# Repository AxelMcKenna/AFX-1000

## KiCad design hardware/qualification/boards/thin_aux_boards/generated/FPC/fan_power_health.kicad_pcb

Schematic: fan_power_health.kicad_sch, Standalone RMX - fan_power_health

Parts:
C1, C2: 10uF 25V C3225X7R1E106K250AC; Capacitor_SMD__C_1210_3225Metric
C3, C14, C22, C23: 10nF 50V C0G C1206C103J5GACTU; Capacitor_SMD__C_1206_3216Metric
C4, C5, C6, C8, C9, C10, C11, C12, C13, C15, C16, C17, C18, C19, C24: 100nF 25V C0G C1206C104J3GACTU; Capacitor_SMD__C_1206_3216Metric
C7: 2.7nF 50V C0G5% C0603C272J5GACTU; Capacitor_SMD__C_0603_1608Metric
C20, C21: 15pF 50V C0G5% C0603C150J5GACTU; Capacitor_SMD__C_0603_1608Metric
C201, C202, C301, C302: 100nF25V C0G5% C1206C104J3GACTU; Capacitor_SMD__C_1206_3216Metric
C203, C303: 1uF63V10% WIMA MKS2C041001F00KSSD; Capacitor_THT__C_Rect_L7.2mm_W5.0mm_P5.00mm
C401, C402, C403, C404: 100nF50V X7R10% C0603C104K5RACTU - EFFECTIVE60nF_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; Capacitor_SMD__C_0603_1608Metric
J2, J3, J4, J201: JST B2B-XH-A / XHP-2 / SXH-001T-P0.6; Connector_JST__JST_XH_B2B-XH-A_1x02_P2.50mm_Vertical
J5: AVRISP2x3 target-powered3.3V sense ONLY; Connector_PinHeader_2.54mm__PinHeader_2x03_P2.54mm_Vertical
J202, J203: JST B3B-XH-A / XHP-3 / SXH-001T-P0.6; Connector_JST__JST_XH_B3B-XH-A_1x03_P2.50mm_Vertical
J401: JST B2B-PH-K-S / PHR-2 / SPH-002T-P0.5S; Connector_JST__JST_PH_B2B-PH-K_1x02_P2.00mm_Vertical
R1, R16, R17, R21, R23: 1k 0.1%25ppm TNPW08051K00BEEA; Resistor_SMD__R_0805_2012Metric
R2, R6, R10, R13, R202, R302: 10k 0.1%25ppm TNPW080510K0BEEA; Resistor_SMD__R_0805_2012Metric
R3, R4, R5, R7, R14, R15: 47k 0.1%25ppm TNPW080547K0BEEA; Resistor_SMD__R_0805_2012Metric
R8: 68k 0.1%25ppm TNPW080568K0BEEA; Resistor_SMD__R_0805_2012Metric
R9: 39k 0.1%25ppm TNPW080539K0BEEA; Resistor_SMD__R_0805_2012Metric
R11: 56.2k 0.1%25ppm TNPW080556K2BEEA; Resistor_SMD__R_0805_2012Metric
R12, R24, R201, R203, R301, R303: 100k 0.1%25ppm TNPW0805100KBEEA; Resistor_SMD__R_0805_2012Metric
R20, R22: 20k 0.1%25ppm TNPW080520K0BEEA; Resistor_SMD__R_0805_2012Metric
R401: 220k 0.1%25ppm TNPW0805220KBEEA - COMPLETE1% RECE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; Resistor_SMD__R_0805_2012Metric
U1: ATtiny84A-SSUR; Package_SO__SOIC-14_3.9x8.7mm_P1.27mm
U2: TPS7A1633DGNR; TI_DGN0008C
U3: SN74LVC2G17DCKR; Package_TO_SOT_SMD__SOT-363_SC-70-6
U4: TPS3431SDRBR; Package_SON__VSON-8-1EP_3x3mm_P0.65mm_EP1.65x2.4mm
U5: SN74AUP1G17DCKR; Package_TO_SOT_SMD__SOT-353_SC-70-5
U6: SN74LVC1T45DBVR; Package_TO_SOT_SMD__SOT-23-6
U7: SN74LVC1G14DCKR; Package_TO_SOT_SMD__SOT-353_SC-70-5
U8: SN74LVC1G74DCUR; TI_DCU0008A
U9: TPS389001DSET; Package_SON__WSON-6_1.5x1.5mm_P0.5mm
U10, U11: SN74LVC1G17DCKR; Package_TO_SOT_SMD__SOT-353_SC-70-5
U12, U13: SN74LVC1G08DCKR; Package_TO_SOT_SMD__SOT-353_SC-70-5
U14: SN74LVC1G06DCKR; Package_TO_SOT_SMD__SOT-353_SC-70-5
U15: TLP175A(TPL,E); RMX_FH02__TLP175A_11-4M1S_Receiving
U16: SN74LVC1G34DCKR; Package_TO_SOT_SMD__SOT-353_SC-70-5
U201, U301: TPS2553DBVR-1; Package_TO_SOT_SMD__SOT-23-6
U401: TPS2553DBVR-1; TI_DBV0006A
X1: ABLS-4.000MHZ-12-D4Y-T; RMX_FH02__ABLS_Manufacturer_Land

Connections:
/E28_POWER_RUN: J4.2 (TO_E28_J5_3), U15.6 (CONTACT_B)
/FAN5V_IN: C1.1, C10.1, C11.1, C12.1, C13.1, C15.1, C201.1, C202.1, C301.1, C302.1, C401.1, C402.1, J201.1 (FAN5V_IN), R1.1, R10.1, R11.1, U2.5 (EN), U2.8 (IN), U6.6 (VCCB), U7.5 (VCC), U8.2 (D), U8.7 (PRE_N), U8.8 (VCC), U9.3 (MR_N), U9.4 (VDD), U10.5 (VCC), U201.1 (IN), U201.3 (EN), U301.1 (IN), U301.3 (EN), U401.1 (IN), U401.3 (EN)
/FAN_L_5V: C203.1, J202.2 (FAN_L_5V), R202.1, R203.1, U201.6 (OUT)
/FAN_L_ILIM: R201.1, U201.5 (ILIM)
/FAN_L_TACH: J202.3 (FAN_L_TACH), R14.1, R202.2, U3.1 (1A)
/FAN_R_5V: C303.1, J203.2 (FAN_R_5V), R302.1, R303.1, U301.6 (OUT)
/FAN_R_ILIM: R301.1, U301.5 (ILIM)
/FAN_R_TACH: J203.3 (FAN_R_TACH), R15.1, R302.2, U3.3 (2A)
/FAULT_CLK: U7.4 (Y), U8.1 (CLK)
/GND: C1.2, C2.2, C3.2, C4.2, C5.2, C6.2, C7.2, C8.2, C9.2, C10.2, C11.2, C12.2, C13.2, C14.2, C15.2, C16.2, C17.2, C18.2, C19.2, C20.2, C21.2, C22.2, C23.2, C24.2, C201.2, C202.2, C203.2, C301.2, C302.2, C303.2, C401.2, C402.2, C403.2, C404.2, J2.2 (GND), J3.2 (GND), J5.6 (GND), J201.2 (FAN_GND), J202.1 (FAN_GND), J203.1 (FAN_GND), J401.2 (GND), R3.2, R4.2, R8.2, R9.2, R12.2, R13.2, R14.2, R15.2, R24.2, R201.2, R203.2, R301.2, R303.2, R401.2, U1.14 (GND), U2.4 (GND), U2.9 (EP), U3.2 (GND), U4.4 (GND), U4.9 (EP), U5.3 (GND), U6.2 (GND), U7.3 (GND), U8.4 (GND), U9.2 (GND), U10.3 (GND), U11.3 (GND), U12.3 (GND), U13.3 (GND), U14.3 (GND), U16.3 (GND), U201.2 (GND), U301.2 (GND), U401.2 (GND)
/HEALTH_AND_WD: U12.4 (Y), U13.1 (A)
/HEARTBEAT: R4.1, U1.11 (PA2), U16.2 (A)
/HEARTBEAT_FAST: U4.6 (WDI), U16.4 (Y)
/HW_NOFAULT: U11.4 (Y), U13.2 (B)
/HW_NOFAULT_5: R9.1, U8.3 (Q_N), U11.2 (A)
/ISP_MISO: J5.1 (ISP_MISO), U1.8 (PA5_MISO)
/ISP_MOSI: J5.4 (ISP_MOSI), U1.7 (PA6_MOSI)
/ISP_SCK: J5.3 (ISP_SCK), U1.9 (PA4_SCK)
/LDO_DELAY: C3.1, U2.7 (DELAY)
/LEAF_PERMISSION: R13.1, U13.4 (Y), U14.2 (A)
/LED_A: R1.2, R2.1, U15.1 (LED_A)
/LED_K: R2.2, U14.4 (Y), U15.3 (LED_K)
/MCU_HEALTH: R3.1, U1.6 (PA7), U12.1 (A)
/MCU_RESET_N: J5.5 (MCU_RESET_N), R6.2, U1.4 (PB3_RESET_N)
/MCU_TACH_L: R16.2, U1.10 (PA3)
/MCU_TACH_R: R17.2, U1.5 (PB2)
/NF_RAW5: C403.1, C404.1, J401.1 (NF_RAW5), U401.6 (OUT)
/NF_RAW5_ILIM: R401.1, U401.5 (ILIM)
/P03_POWER_RUN: J4.1 (FROM_P03_J106_3), U15.4 (CONTACT_A)
/RAW_CLEAR_FAST: U8.6 (CLR_N), U10.4 (Y)
/RAW_CLEAR_N: R10.2, U9.6 (RESET_N), U10.2 (A)
/RAW_POR_CT: C14.1, U9.5 (CT)
/RAW_POR_SENSE: R11.2, R12.1, U9.1 (SENSE)
/TACH_L_BUF: R16.1, U3.6 (1Y)
/TACH_R_BUF: R17.1, U3.4 (2Y)
/TEMP_L_ADC: C22.1, R21.2, U1.13 (PA0_ADC0)
/TEMP_L_NODE: J2.1 (SENSOR), R20.2, R21.1
/TEMP_R_ADC: C23.1, R23.2, U1.12 (PA1_ADC1)
/TEMP_R_NODE: J3.1 (SENSOR), R22.2, R23.1
/V3V3: C2.1, C4.1, C5.1, C6.1, C8.1, C9.1, C16.1, C17.1, C18.1, C19.1, C24.1, J5.2 (V3V3), R5.1, R6.1, R7.1, R20.1, R22.1, R24.1, U1.1 (VCC), U2.1 (OUT), U3.5 (VCC), U4.1 (VDD), U4.5 (SET1), U5.5 (VCC), U6.1 (VCCA), U6.5 (DIR), U11.5 (VCC), U12.5 (VCC), U13.5 (VCC), U14.5 (VCC), U16.5 (VCC)
/WD_CWD: C7.1, U4.2 (CWD)
/WD_EN: R7.2, U4.3 (EN)
/WD_OK: R5.2, U2.3 (PG), U4.7 (WDO_N), U4.8 (ENOUT), U5.2 (A)
/WD_OK_5: R8.1, U6.4 (B), U7.2 (A)
/WD_OK_FAST: U5.4 (Y), U6.3 (A), U12.2 (B)
/XTAL1: C20.1, U1.2 (PB0_XTAL1), X1.1 (XTAL1)
/XTAL2: C21.1, U1.3 (PB1_XTAL2), X1.2 (XTAL2)

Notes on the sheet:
FPC_M2 private successor: third protected NF RAW5 leaf; all84 parent circuits/poses unchanged.
RAW5 operating P03J23/J21 ONLY, neverTESTJ3. No full-source/inrush/physical/PDN acceptance.

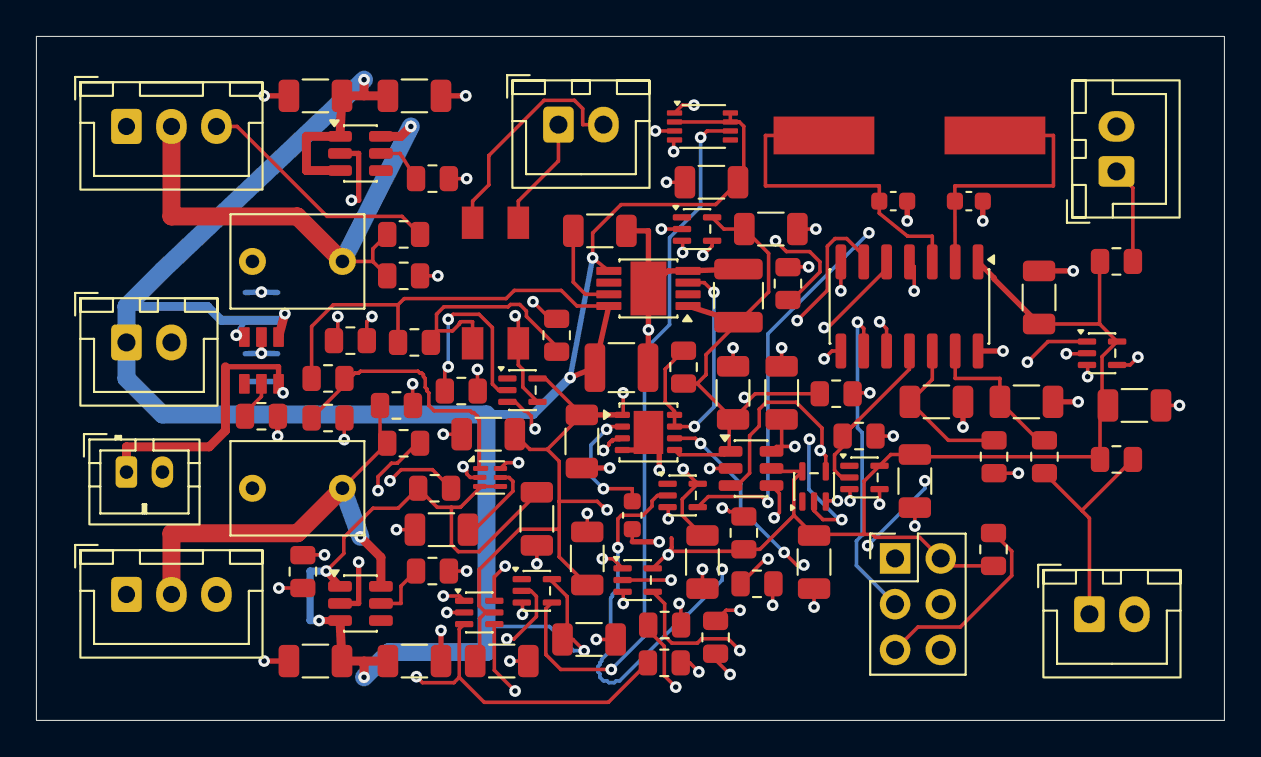
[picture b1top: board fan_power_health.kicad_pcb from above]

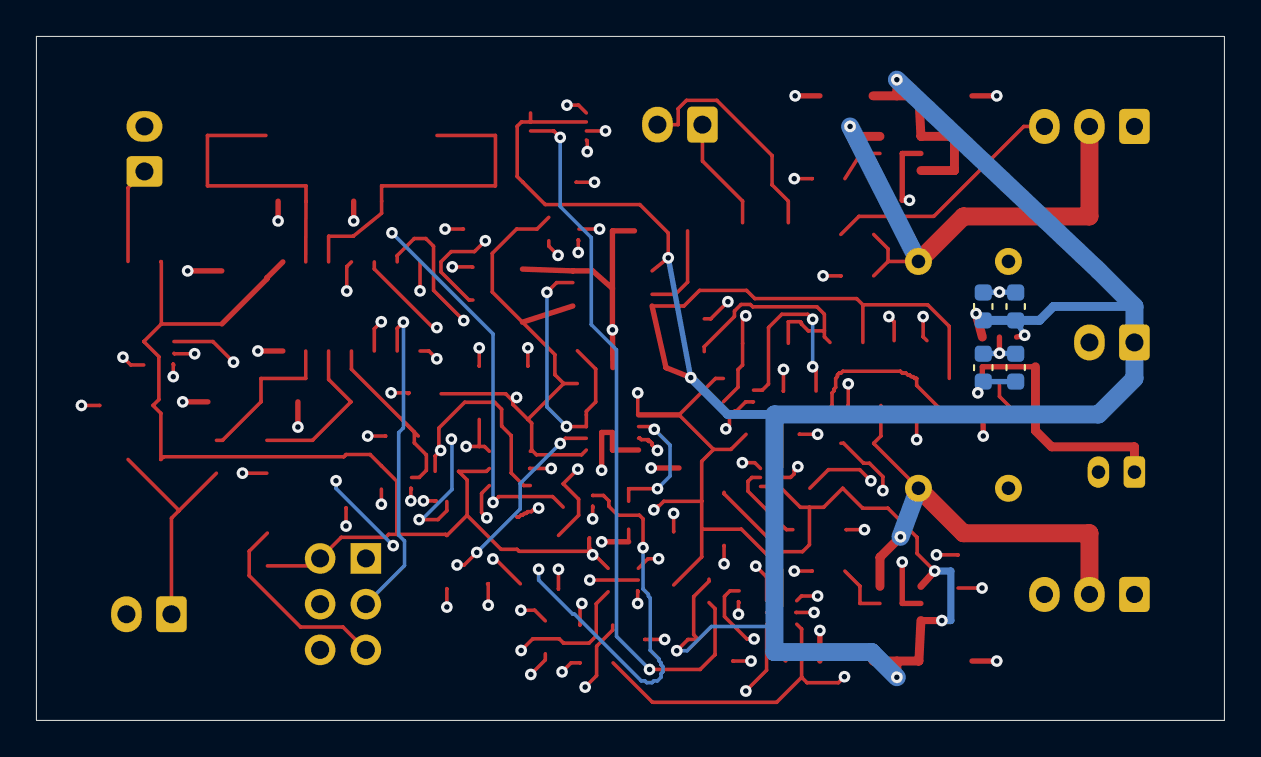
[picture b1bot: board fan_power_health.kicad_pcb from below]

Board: 4 copper layers, 66.0 x 38.0 mm, 91 parts (4 on the bottom side), 47 nets.

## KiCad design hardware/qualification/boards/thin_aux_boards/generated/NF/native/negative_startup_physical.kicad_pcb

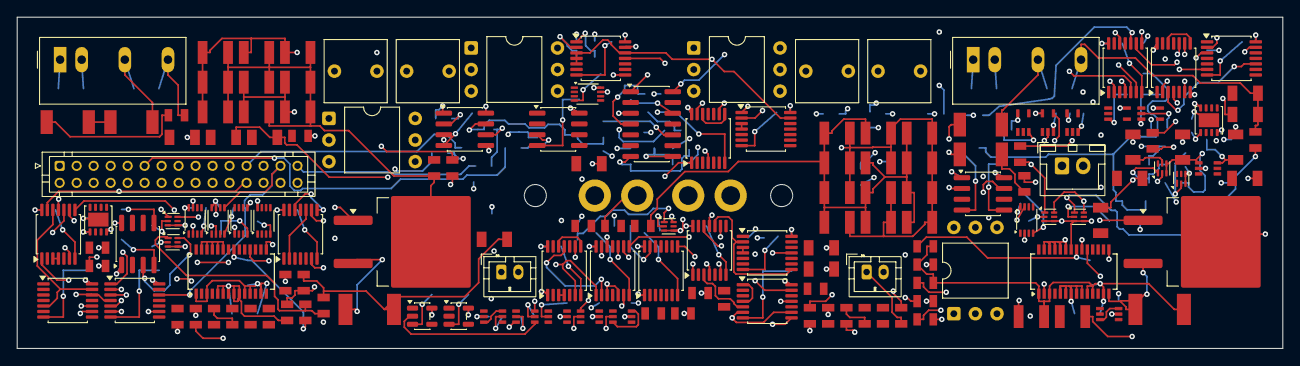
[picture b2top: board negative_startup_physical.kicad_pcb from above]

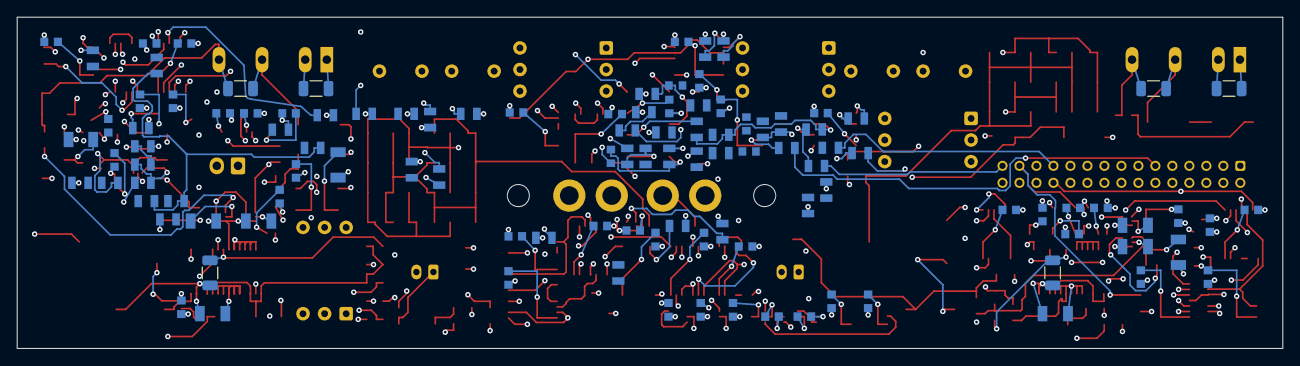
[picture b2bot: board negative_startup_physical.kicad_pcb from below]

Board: 6 copper layers, 149.0 x 39.0 mm, 267 parts (111 on the bottom side), 210 nets.

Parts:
C1: 56nF50V C0G5% C1206C563J5GACTU - COMPLETE10% RECE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; PROPOSED_KEMET1206_LevelB
C2: 33nF50V C0G5% C1206C333J5GACTU - COMPLETE10% RECE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; PROPOSED_KEMET1206_LevelB
C3, C12, C39, C55, C56, C57, C58, C59, C60, C61, C62, C63, C64, C65, C66, C67, C68, C69, C70, C71, C72, C73, C74, C75, C76, C77, C78, C79, C80, C81, C82, C83, C84, C85, C86, C87, C88: 100nF 50V X7R10% C0603C104K5RACTU - bypass effect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; PROPOSED_KEMET0603_LevelB
C4, C31: 10uF 25V X7R MODULE INPUT FILTER/EFFECTIVE/INRUSH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; Capacitor_SMD__C_1206_3216Metric
C5, C32: 1uF 50V X7R MODULE OUTPUT FILTER/EFFECTIVE HOLD; Capacitor_SMD__C_1206_3216Metric
C6, C33: 1uF 25V X7R LTC4261 local VIN effective HOLD; Capacitor_SMD__C_1206_3216Metric
C7, C9, C11, C13, C34, C36, C38, C40: 100nF 25V C0G C1206C104J3GACTU; PROPOSED_KEMET1206_LevelB
C8, C10, C35, C37: 10nF 50V C0G COMPLETE10% TIMING RECEIVING; PROPOSED_KEMET1206_LevelB
C14, C15, C16, C17, C18, C19, C20, C21, C22, C23, C24, C25, C41, C42, C43, C44, C45, C46, C47, C48, C49: 100nF 50V C0G C1210C104J5GACTU - COMPLETE10% RAMP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; PROPOSED_KEMET1210_LevelB
C26, C27, C50, C51: 2.2uF 63V PET5% MKS2C042201K00JSSD - COMPLETE10% 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; Capacitor_THT__C_Rect_L7.2mm_W7.2mm_P5.00mm_FKS2_FKP2_MKS2_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
C28, C30, C52, C54: 47nF 50V C0G C1206C473J5GACTU; PROPOSED_KEMET1206_LevelB
C29, C53: 100nF 50V C0G C1210C104J5GACTU; PROPOSED_KEMET1210_LevelB
C89, C90, C91, C93, C94, C96: 100nF50V X7R10% C0603C104K5RACTU - EFFECTIVE/PDN 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; PROPOSED_KEMET0603_LevelB
C92, C95: 47nF50V C0G5% C1206C473J5GACTU - COMPLETE6% RECEI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; PROPOSED_KEMET1206_LevelB
C97, C98: 100nF25V C0G5% C1206C104J3GACTU - COMPLETE6% CT /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; PROPOSED_KEMET1206_LevelB
C99: 100nF25V C0G5% C1206C104J3GACTU - COMPLETE6% UVRE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; PROPOSED_KEMET1206_LevelB
C100: 100nF50V X7R10% C0603C104K5RACTU - LOCAL_BYPASS_E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; PROPOSED_KEMET0603_LevelB
H101, H102: STRAIN_POST_2p6_NPTH_RECEIVING
J1: NEW NF03C CONTROL/KELVIN INTERFACE - physical con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; NC265_JST_PHD_B30B-PHDSS_2x15_P2.00mm_Vertical
J2: N19 NEW FORCE IN/OUT - connector and harness unse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; NC265_NC265_Force2_18AWG_P5_Drill2p2_Land3p8
J3: N19 E28 BANK GATE/COMMON CLAMP - physical interfa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; NC265_JST_PH_B2B-PH-K_1x02_P2.00mm_Vertical
J4: N12 NEW FORCE IN/OUT - connector and harness unse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; NC265_NC265_Force2_18AWG_P5_Drill2p2_Land3p8
J5: N12 E28 BANK GATE/COMMON CLAMP - physical interfa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; NC265_JST_PH_B2B-PH-K_1x02_P2.00mm_Vertical
J6: NEW MODULE INPUT ONLY - keyed JST XH2 receiving c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; NC265_JST_XH_B2B-XH-A_1x02_P2.50mm_Vertical
Q1, Q2: CSD19536KTT; Package_TO_SOT_SMD__TO-263-2
R1, R2, R8, R9: 10k; PROPOSED_TNPW0805_IPC28950
R3, R10: 205000ohm 0.1% TNPW0805205KBEEA - COMPLETE3% RECE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; PROPOSED_TNPW0805_IPC28950
R4, R11: 499ohm 0.1% TNPW0805499RBEEA - COMPLETE3% RECEIVI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; PROPOSED_TNPW0805_IPC28950
R5, R12, R95, R98, R99: 10000ohm 0.1% TNPW080510K0BEEA - COMPLETE3% RECEI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; PROPOSED_TNPW0805_IPC28950
R6, R7, R13, R14: 220ohm COMPLETE +/-3% RECEIVING; PROPOSED_TNPW0805_IPC28950
R15, R16, R17, R18, R19, R20, R21, R22: 47k 3% TOTAL RECEIVING; PROPOSED_TNPW0805_IPC28950
R23: 160000ohm COMPLETE0.1% RECEIVING; PROPOSED_TNPU0805_IPC28950
R24, R41, R63, R65, R80, R82: 10k COMPLETE0.1% RECEIVING; PROPOSED_TNPU0805_IPC28950
R25, R49: 8660ohm COMPLETE0.1% RECEIVING; PROPOSED_TNPU0805_IPC28950
R26, R50: 35.7ohm COMPLETE0.1% RECEIVING; PROPOSED_TNPU0603_IPC28950
R27, R31, R35, R44, R47, R51: 100k COMPLETE0.1% RECEIVING; PROPOSED_TNPU0805_IPC28950
R28, R32, R36, R37, R38, R39, R45, R48, R52, R53, R54, R55, R59, R76: 10k COMPLETE3% RECEIVING; PROPOSED_TNPW0805_IPC28950
R29, R46: 2000ohm COMPLETE0.1% RECEIVING; PROPOSED_TNPU0805_IPC28950
R30: 40.2ohm COMPLETE0.1% RECEIVING; PROPOSED_TNPU0603_IPC28950
R33: 6040ohm COMPLETE0.1% RECEIVING; PROPOSED_TNPU0805_IPC28950
R34: 75ohm COMPLETE0.1% RECEIVING; PROPOSED_TNPU0603_IPC28950
R40: 102000ohm COMPLETE0.1% RECEIVING; PROPOSED_TNPU0805_IPC28950
R42: 10700ohm COMPLETE0.1% RECEIVING; PROPOSED_TNPU0805_IPC28950
R43: 169ohm COMPLETE0.1% RECEIVING; PROPOSED_TNPU0805_IPC28950
R56, R57, R73, R74: 402ohm 1% CRCW2010402RFKEF - COMPLETE3% RECEIVING; PROPOSED_CRCW2010_reflow20035
R58, R60, R61, R66, R67, R68, R75, R77, R78, R83, R84, R85: 47k COMPLETE3% RECEIVING; PROPOSED_TNPW0805_IPC28950
R62, R79: 30.4k COMPLETE0.1% RECEIVING; PROPOSED_TNPU0805_IPC28950
R64, R81: 78.7k COMPLETE0.1% RECEIVING; PROPOSED_TNPU0805_IPC28950
R69: 0.33ohm COMPLETE5% SHUNT RECEIVING; PROPOSED_WSL2512_7m_to500m
R70, R87: 10ohm COMPLETE3% RECEIVING; PROPOSED_TNPW0805_IPC28950
R71, R88: 1M; PROPOSED_TNPW0805_IPC28950
R72: 27ohm COMPLETE3% RECEIVING; PROPOSED_TNPW0805_IPC28950
R86: 0.12ohm COMPLETE5% SHUNT RECEIVING; PROPOSED_WSL2512_7m_to500m
R89: 39ohm COMPLETE3% RECEIVING; PROPOSED_TNPW0805_IPC28950
R90, R91: 10k0.1% TNPW080510K0BEEA - COMPLETE3% RECEIVING; PROPOSED_TNPW0805_IPC28950
R92: 11300ohm 0.02% 2ppm TNPU080511K3HWEN00 - COMPLETE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; PROPOSED_TNPW0805_IPC28950
R93: 49.9ohm 0.1% TNPW080549R9BEEA - COMPLETE0.7% TRIM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; PROPOSED_TNPW0805_IPC28950
R94: 10000ohm 0.02% 2ppm TNPU080510K0HWEN00 - COMPLETE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; PROPOSED_TNPW0805_IPC28950
R96: 47000ohm 0.1% TNPW080547K0BEEA - COMPLETE3% RECEI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; PROPOSED_TNPW0805_IPC28950
R97: 680ohm 0.1% TNPW1206680RBEEA - COMPLETE3% RECEIVI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; PROPOSED_TNPW1206_IPC28950
U1, U2, U7, U8: SN74AUP1G74DCUR; NF05R_Manufacturer__TI_DCU0008A
U3, U9: TPS3431SDRBR; Package_SON__VSON-8-1EP_3x3mm_P0.65mm_EP1.65x2.4mm
U4, U10: SN74LVC1G06DBVR; Package_TO_SOT_SMD__SOT-23-5
U5, U6, U11, U12: TLP4590AF(F; Package_DIP__DIP-6_W10.16mm
U13: OPA2333AID; Package_SO__SOIC-8_3.9x4.9mm_P1.27mm
U14: TLV1822DR; Package_SO__SOIC-8_3.9x4.9mm_P1.27mm
U15: TLV1824DR; Package_SO__SOIC-14_3.9x8.7mm_P1.27mm
U16, U27: SN74LVC2T45DCUR; NF05R_Manufacturer__TI_DCU0008A
U17, U22: TMR 1-1215; Converter_DCDC__Converter_DCDC_TRACO_TMR-1-xxxx_Single_THT
U18, U23: LTC4261IGN#PBF; Package_SO__SSOP-28_3.9x9.9mm_P0.635mm
U19, U24: ISO7721FDR; Package_SO__SOIC-8_3.9x4.9mm_P1.27mm
U20, U21, U25, U26, U52, U54, U56: TPS389001DSET; Package_SON__WSON-6_1.5x1.5mm_P0.5mm
U28, U30, U53, U55: SN74LVC1G17DCKR; NF05R_Manufacturer__TI_DCK0005A
U29, U31, U32, U33, U34, U49: SN74AUP2G14DCKR; NF05R_Manufacturer__TI_DCK0006A
U35, U36, U37, U38, U39, U40, U41, U42, U43, U44, U51: SN74HCS08PWR; Package_SO__TSSOP-14_4.4x5mm_P0.65mm
U45, U46: SN74HCS32PWR; Package_SO__TSSOP-14_4.4x5mm_P0.65mm
U47, U48: SN74HCS14PWR; Package_SO__TSSOP-14_4.4x5mm_P0.65mm
U50: SN74HCS02PWR; Package_SO__TSSOP-14_4.4x5mm_P0.65mm
U57: TPS22919DCKR; NF05R_Manufacturer__TI_DCK0006A
U58: SN74LVC1G14DCKR; NF05R_Manufacturer__TI_DCK0005A

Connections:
/ABS_AUX_CT: C99.1, U56.5
/ABS_AUX_FAULT: J1.7, R17.1, U48.13, U58.4
/ABS_AUX_READY: U48.12, U51.13
/ABS_AUX_SENSE: R93.2, R94.1, U56.1
/ABS_AUX_TOP_TRIM: R92.2, R93.1
/AGND: C1.2, C2.2, C3.2, C12.2, C39.2, C55.2, C56.2, C57.2, C58.2, C59.2, C60.2, C61.2, C62.2, C63.2, C64.2, C65.2, C66.2, C67.2, C68.2, C69.2, C70.2, C71.2, C72.2, C73.2, C74.2, C75.2, C76.2, C77.2, C78.2, C79.2, C80.2, C81.2, C82.2, C83.2, C84.2, C85.2, C86.2, C87.2, C88.2, C89.2, C90.2, C91.2, C92.2, C93.2, C94.2, C95.2, C96.2, C97.2, C98.2, C99.2, C100.2, J1.2, R3.2, R10.2, R15.2, R16.2, R17.2, R18.2, R19.2, R20.2, R21.2, R22.2, R27.2, R31.2, R35.2, R44.2, R47.2, R51.2, R59.2, R61.2, R67.2, R68.2, R76.2, R78.2, R84.2, R85.2, R94.2, R96.2, R97.2, U1.4, U2.4, U3.4, U3.9, U4.3, U7.4, U8.4, U9.4, U9.9, U10.3, U13.3, U13.4, U13.5, U14.4, U15.12, U16.4, U19.5, U24.5, U27.4, U28.3, U29.2, U30.3, U31.2, U32.2, U33.2, U34.2, U35.7, U36.7, U37.7, U38.7, U39.7, U40.7, U41.7, U42.7, U43.7, U44.7, U45.7, U46.7, U46.12, U46.13, U47.7, U48.7, U49.2, U50.7, U51.7, U52.2, U53.3, U54.2, U55.3, U56.2, U57.2, U58.3
/AUX2V6: C3.1, C12.1, C56.1, C57.1, C58.1, C59.1, C60.1, C61.1, C62.1, C63.1, C64.1, C65.1, C66.1, C67.1, C68.1, C69.1, C70.1, C71.1, C72.1, C73.1, C74.1, C75.1, C76.1, C77.1, C78.1, C79.1, C80.1, C81.1, C82.1, C83.1, C84.1, C85.1, C86.1, C87.1, C88.1, C89.1, C90.1, C91.1, C93.1, C94.1, C96.1, C100.1, J1.1, R1.1, R2.1, R8.1, R9.1, R37.1, R38.1, R39.1, R53.1, R54.1, R55.1, R90.1, R91.1, R92.1, U1.7, U1.8, U2.2, U2.7, U2.8, U3.1, U4.5, U7.7, U7.8, U8.2, U8.7, U8.8, U9.1, U10.5, U13.8, U14.8, U15.3, U16.1, U16.5, U27.8, U28.5, U29.5, U30.5, U31.5, U32.5, U33.5, U34.5, U35.14, U36.14, U37.14, U38.14, U39.14, U40.14, U41.14, U42.14, U43.14, U44.14, U45.14, U46.14, U47.14, U48.14, U49.5, U50.14, U51.14, U52.3, U52.4, U53.5, U54.3, U54.4, U55.5, U58.5
/AUX_VALID: J1.5, R16.1, U35.1
/CLAMP_LED_SUPPLY: C98.1, R4.1, R11.1, R97.1, U57.6
/CLAMP_SUPPLY_ENABLE: R95.2, R96.1, U56.6, U57.3, U58.2
/DIG5_FORCE: C39.1, C55.1, C97.1, J1.3, R95.1, U16.8, U19.8, U24.8, U27.1, U27.5, U56.3, U56.4, U57.1
/E28_COMBINED_FAULT_REQUEST: J1.14, U34.4
/E28_COMBINED_FAULT_REQUEST_BUFFER_MID: U34.3, U34.6
/E28_COMBINED_FAULT_REQUEST_HCS: U34.1, U46.6
/E28_NATIVE_FAULT_REQUEST: J1.13, U46.4
/E28_NOT_FAULT: J1.15, R22.1, U44.4
/GLOBAL_MASTER: J1.6, R15.1, U35.2
/GLOBAL_VALID: U35.3, U35.4, U35.5, U35.12, U37.4, U38.5, U38.13, U40.12, U41.13, U48.11, U51.1, U51.4
/GUARDED_12V_FORCE: C4.1, C31.1, J6.1, U17.2, U22.2
/MODULE_INPUT_GND: C4.2, C31.2, J6.2, U17.1, U22.1
/N12_ARM_CONDITIONED: J1.24, R20.1, U30.4, U39.1, U40.13, U41.12, U54.1
/N12_ARM_Q: U30.2, U50.10, U50.12
/N12_ARM_QBAR: U50.9, U50.13
/N12_ARM_SET: U50.11, U51.8
/N12_BANK_CLAMP_GATE: R14.2, U12.4
/N12_BANK_COMMON: J5.2, U12.6
/N12_BANK_GATE: J5.1, R14.1
/N12_BIAS_CT: C37.1, U25.5
/N12_BIAS_HOST5: R84.1, U24.6, U27.3
/N12_BIAS_RESET_N: R83.2, U24.3, U25.6, U26.6
/N12_BIAS_SENSE: R79.2, R80.1, U25.1
/N12_BIAS_VALID: J1.17, R85.1, U27.6, U43.13
/N12_CG_SERIES: C52.1, R87.2
/N12_CLAMPS_RELEASE: J1.28, R10.1, U10.2, U33.4
/N12_CLAMPS_RELEASE_BUFFER_MID: U33.3, U33.6
/N12_CLAMPS_RELEASE_HCS: U33.1, U42.3
/N12_CLAMP_LED_A: R11.2, R12.1, U11.1
/N12_CLAMP_LED_K: R99.2, U10.4, U12.2
/N12_CLAMP_LED_MID: R12.2, R99.1, U11.2, U12.1
/N12_COMPLETE: J1.27, U8.5, U39.12, U44.12
/N12_COMPLETE_CLK: U8.1, U41.8
/N12_COMPLETE_CLR_N: U8.6, U41.11
/N12_CONTROLLER_ON: R77.1, U23.2, U24.2
/N12_CR_TOP: C41.1, C42.1, C43.1, C44.1, C45.1, C46.1, C47.1, C48.1, C49.1, R89.2
/N12_CWD: C2.1, U9.2
/N12_DRAIN_SENSE: R88.2, U23.16
/N12_E28_SRC: C41.2, C42.2, C43.2, C44.2, C45.2, C46.2, C47.2, C48.2, C49.2, J4.2, Q2.2, R88.1
/N12_F0: U45.8, U45.12
/N12_FAULT_REQUEST: J1.26, U45.11, U46.2
/N12_FEED_MID: R73.2, R74.1
/N12_F_OUTPUT: U39.11, U45.13
/N12_F_SOURCE: U39.3, U45.9
/N12_F_TIMEOUT: U39.8, U45.10
/N12_F_WD_ARM: U39.6, U39.9
/N12_INTVCC: C34.1, C36.1, C38.1, C40.1, R79.1, R83.1, U23.5, U23.6, U23.7, U23.8, U23.9, U23.22, U24.1, U25.3, U25.4, U26.3, U26.4
/N12_ISO24: C32.1, R73.1, U22.4
/N12_NOT_COMPLETE: U8.3, U9.5
/N12_NOT_PERMIT: U7.3, U9.6
/N12_NOT_READY: U39.13, U47.10
/N12_NOT_SAFE: U39.2, U47.8
/N12_NOT_WDO: U39.10, U47.12
/N12_OUTPUT_OV_GOOD: R55.2, U15.13, U43.10, U44.2
/N12_OUTPUT_QUALIFIED: U44.11, U48.5
/N12_OUTPUT_UV_GOOD: R54.2, U15.14, U44.1
/N12_OUT_INV: R41.1, R45.1, R48.1, U13.7
/N12_OUT_OV_REF: R46.2, R47.1, U15.11
/N12_OUT_OV_SENSE: R48.2, U15.10
/N12_OUT_SUM: R40.2, R41.2, U13.6
/N12_OUT_UV_REF: R43.2, R44.1, U15.8
/N12_OUT_UV_RMID: R42.2, R43.1
/N12_OUT_UV_SENSE: R45.2, U15.9
/N12_OV_OK: J1.10, U43.5
/N12_OV_SENSE: J1.12, R52.1
/N12_P03_SRC: C32.2, C33.2, C34.2, C35.2, C36.2, C37.2, C38.2, C40.2, C50.2, C51.2, C52.2, C53.2, C54.2, J4.1, R75.2, R76.1, R77.2, R80.2, R82.2, R86.1, U22.6, U23.1, U23.3, U23.10, U23.11, U23.13, U23.23, U23.24, U23.25, U23.26, U23.27, U24.4, U25.2, U26.2
/N12_PASS_CLAMP_GATE: R13.2, U11.4
/N12_PASS_GATE: Q2.1, R13.1, R87.1, U23.15
/N12_PASS_SOURCE: Q2.3, R86.2, U11.6, U23.14
/N12_PCLR0: U40.11, U41.1, U42.1
/N12_PCLR1: U41.3, U41.4
/N12_PERMIT: U7.5, U16.3, U41.9
/N12_PERMIT_CLR_N: U7.6, U41.6
/N12_PERMIT_D: U7.2, U40.8, U51.10
/N12_PROTECTED: J1.29, R40.1
/N12_RAMP: C50.1, C51.1, R89.1, U23.18
/N12_READY: U41.10, U44.3, U44.13, U47.11
/N12_RUN_HOST5: R78.1, U16.6, U24.7
/N12_SAFE: U40.5, U41.5, U43.11, U47.9
/N12_SOURCE_SAFE0: U43.6, U43.9
/N12_SOURCE_SAFE1: U43.8, U43.12
/N12_SOURCE_UV_GOOD: R53.2, U14.7, U43.4
/N12_SOURCE_UV_REF: R50.2, R51.1, U14.6
/N12_SOURCE_UV_RMID: R49.2, R50.1
/N12_SOURCE_UV_SENSE: R52.2, U14.5
/N12_SS: C53.1, U23.19
/N12_STAGE_ENABLED: U38.12, U39.4, U51.6, U51.9
/N12_START: J1.25, R21.1, U31.1, U55.4
/N12_START_ARMED: U40.3, U40.4
/N12_START_CONDITIONED: U7.1, U31.4
/N12_START_CONDITIONED_BUFFER_MID: U31.3, U31.6
/N12_START_CT: C95.1, U54.5
/N12_START_DELAY_N: R91.2, U54.6, U55.2
/N12_START_SAFE: U40.6, U40.9
/N12_TMR: C54.1, U23.20
/N12_VIN: C33.1, R74.2, R75.1, R81.1, U23.21
/N12_VIN_VALID_CT: C35.1, U26.5
/N12_VIN_VALID_SENSE: R81.2, R82.1, U26.1
/N12_WDO: R8.2, U9.7, U40.2, U47.13
/N12_WD_ARMED: R9.2, U9.8, U39.5, U40.1
/N12_WD_ENABLE: U9.3, U38.11
/N19_ARM_CONDITIONED: J1.18, R18.1, U28.4, U35.9, U37.5, U38.4, U52.1
/N19_ARM_Q: U28.2, U50.1, U50.6
/N19_ARM_QBAR: U50.3, U50.4
/N19_ARM_SET: U50.5, U51.3
/N19_BANK_CLAMP_GATE: R7.2, U6.4
/N19_BANK_COMMON: J3.2, U6.6
/N19_BANK_GATE: J3.1, R7.1
/N19_BIAS_CT: C10.1, U20.5
/N19_BIAS_HOST5: R67.1, U19.6, U27.2
/N19_BIAS_RESET_N: R66.2, U19.3, U20.6, U21.6
/N19_BIAS_SENSE: R62.2, R63.1, U20.1
/N19_BIAS_VALID: J1.16, R68.1, U27.7, U42.13
/N19_CG_SERIES: C28.1, R70.2
/N19_CLAMPS_RELEASE: J1.22, R3.1, U4.2, U32.4
/N19_CLAMPS_RELEASE_BUFFER_MID: U32.3, U32.6
/N19_CLAMPS_RELEASE_HCS: U32.1, U38.8
/N19_CLAMP_LED_A: R4.2, R5.1, U5.1
/N19_CLAMP_LED_K: R98.2, U4.4, U6.2
/N19_CLAMP_LED_MID: R5.2, R98.1, U5.2, U6.1
/N19_COMPLETE: J1.21, U2.5, U36.4, U44.9
/N19_COMPLETE_CLK: U2.1, U38.3
/N19_COMPLETE_CLR_N: U2.6, U38.6
/N19_CONTROLLER_ON: R60.1, U18.2, U19.2
/N19_CR_TOP: C14.1, C15.1, C16.1, C17.1, C18.1, C19.1, C20.1, C21.1, C22.1, C23.1, C24.1, C25.1, R72.2
/N19_CWD: C1.1, U3.2
/N19_DRAIN_SENSE: R71.2, U18.16
/N19_E28_SRC: C14.2, C15.2, C16.2, C17.2, C18.2, C19.2, C20.2, C21.2, C22.2, C23.2, C24.2, C25.2, J2.2, Q1.2, R71.1
/N19_F0: U45.3, U45.4
/N19_FAULT_REQUEST: J1.20, U45.6, U46.1
/N19_FEED_MID: R56.2, R57.1
/N19_F_OUTPUT: U36.6, U45.5
/N19_F_SOURCE: U35.8, U45.1
/N19_F_TIMEOUT: U36.3, U45.2
/N19_F_WD_ARM: U35.11, U36.1
/N19_INTVCC: C7.1, C9.1, C11.1, C13.1, R62.1, R66.1, U18.5, U18.6, U18.7, U18.8, U18.9, U18.22, U19.1, U20.3, U20.4, U21.3, U21.4
/N19_ISO24: C5.1, R56.1, U17.4
/N19_NOT_COMPLETE: U2.3, U3.5
/N19_NOT_PERMIT: U1.3, U3.6
/N19_NOT_READY: U36.5, U47.4
/N19_NOT_SAFE: U35.10, U47.2
/N19_NOT_WDO: U36.2, U47.6
/N19_OUTPUT_OV_GOOD: R39.2, U15.1, U42.10, U43.2
/N19_OUTPUT_QUALIFIED: U44.8, U48.3, U51.5
/N19_OUTPUT_UV_GOOD: R38.2, U15.2, U43.1
/N19_OUT_INV: R24.1, R28.1, R32.1, U13.1
/N19_OUT_OV_REF: R30.2, R31.1, U15.7
/N19_OUT_OV_RMID: R29.2, R30.1
/N19_OUT_OV_SENSE: R32.2, U15.6
/N19_OUT_SUM: R23.2, R24.2, U13.2
/N19_OUT_UV_REF: R26.2, R27.1, U15.4
/N19_OUT_UV_RMID: R25.2, R26.1
/N19_OUT_UV_SENSE: R28.2, U15.5
/N19_OV_OK: J1.9, U42.5
/N19_OV_SENSE: J1.11, R36.1
/N19_P03_SRC: C5.2, C6.2, C7.2, C8.2, C9.2, C10.2, C11.2, C13.2, C26.2, C27.2, C28.2, C29.2, C30.2, J2.1, R58.2, R59.1, R60.2, R63.2, R65.2, R69.1, U17.6, U18.1, U18.3, U18.10, U18.11, U18.13, U18.23, U18.24, U18.25, U18.26, U18.27, U19.4, U20.2, U21.2
/N19_PASS_CLAMP_GATE: R6.2, U5.4
/N19_PASS_GATE: Q1.1, R6.1, R70.1, U18.15
/N19_PASS_SOURCE: Q1.3, R69.2, U5.6, U18.14
/N19_PCLR0: U37.6, U37.9, U38.9
/N19_PCLR1: U37.8, U37.12
/N19_PERMIT: U1.5, U16.2, U38.1
/N19_PERMIT_CLR_N: U1.6, U37.11
/N19_PERMIT_D: U1.2, U37.3, U51.2
/N19_PROTECTED: J1.23, R23.1
/N19_RAMP: C26.1, C27.1, R72.1, U18.18
/N19_READY: U38.2, U43.3, U44.10, U47.3
/N19_RUN_HOST5: R61.1, U16.7, U19.7
/N19_SAFE: U36.13, U37.13, U47.1, U51.11
/N19_SAFE_SOURCE: U42.11, U51.12
/N19_SOURCE_SAFE0: U42.6, U42.9
/N19_SOURCE_SAFE1: U42.8, U42.12
/N19_SOURCE_UV_GOOD: R37.2, U14.1, U42.4
/N19_SOURCE_UV_REF: R34.2, R35.1, U14.2
/N19_SOURCE_UV_RMID: R33.2, R34.1
/N19_SOURCE_UV_SENSE: R36.2, U14.3
/N19_SS: C29.1, U18.19
/N19_START: J1.19, R19.1, U29.1, U53.4
/N19_START_ARMED: U36.8, U36.12
/N19_START_CONDITIONED: U1.1, U29.4
/N19_START_CONDITIONED_BUFFER_MID: U29.3, U29.6
/N19_START_CT: C92.1, U52.5
/N19_START_DELAY_N: R90.2, U52.6, U53.2
/N19_START_SAFE: U36.11, U37.1
/N19_TMR: C30.1, U18.20
/N19_VIN: C6.1, R57.2, R58.1, R64.1, U18.21
/N19_VIN_VALID_CT: C8.1, U21.5
/N19_VIN_VALID_SENSE: R64.2, R65.1, U21.1
/N19_WDO: R1.2, U3.7, U36.10, U47.5
/N19_WD_ARMED: R2.2, U3.8, U35.13, U36.9
/N19_WD_ENABLE: U3.3, U35.6
/NF_FAULT_REQUEST: U46.3, U46.5, U48.1
/NF_NOT_OUTPUT_VALID: U46.8, U48.9
/NF_NO_FAULT: U37.2, U37.10, U38.10, U40.10, U41.2, U42.2, U44.6
/NF_OUTPUT_VALID: J1.30, U49.4
/NF_OUTPUT_VALID_BUFFER_MID: U49.3, U49.6
/NF_OUTPUT_VALID_HCS: U48.8, U49.1
/NOT_GLOBAL_VALID: U48.10, U50.2, U50.8
/NOT_N12_OUTPUT_QUALIFIED: U46.10, U48.6
/NOT_N19_OUTPUT_QUALIFIED: U46.9, U48.4
/NOT_NF_FAULT_REQUEST: U44.5, U48.2
/PROTECT_REF: J1.8, R25.1, R29.1, R33.1, R42.1, R46.1, R49.1
